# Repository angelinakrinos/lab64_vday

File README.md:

# **Lab64 Valentine's Day Music Box 🎵❤️**  
An Arduino-controlled music player for a Lab64 workshop, using an **ESP32C6**, **DFPlayer Mini**, and **RFID module** to create a customizable music box.

## **Workshop Instructions**  

### **Hardware Setup**  
#### 🔧 **Soldering Your Board**  
1. **Microcontroller (XIAO ESP32C6)**  
   - The **battery pads** on the back should be soldered first.  
   - Apply a small amount of solder to the pads before attaching the leads.  
   - Ensure the leads are inserted into the **thru holes** marked **BAT- and BAT+** (they are swapped—**double-check polarity!**).  
   - Solder header pins onto the microcontroller.  

2. **RFID Module**  
   - Solder **longer header pins** into your RFID module for better connection.  

3. **Soldering Components Onto the Board**  
   - **Terminal blocks** should face **outward** so wires can be easily inserted.  
   - The **battery holder** has clearly marked **positive and negative terminals**—pay attention to **snap-in orientation**.  
   - **RFID module** should be soldered as high as possible for better range.  

4. **Connecting Wires**  
   - Terminal blocks will connect to wires, which will connect to your peripherals (speaker, potentiometer, buttons, etc.).  

---

### **Software Setup**  
#### 💻 **Preparing Your Development Environment**  
1. Install **Arduino IDE** (if you haven’t already).  
2. Install the **XIAO ESP32C6 board configuration** in the Arduino IDE.  

#### 🚀 **Uploading the Code**  
- You need to **push the `vday_lab64_workshop_main.ino` code** to your **ESP32C6** for the music box to function.  
- Open `lab64_vday.ino` in Arduino IDE, select the correct **board (ESP32C6)** and **port**, then upload the code.  

#### 📀 **Writing RFID Tags & Playing Music**  
1. **RFID Writing**  
   - Use the provided `rfid_writer.ino` code to write RFID tags.  
   - The writer will **batch-write** tags **sequentially from 1 → ∞** (keep swiping cards to keep writing).  

2. **Music File Setup**  
   - Format your **microSD card to FAT32**.  
   - Inside the SD card, create a folder named **`mp3`**.  
   - Add your MP3 files inside the folder, naming them sequentially:  
     ```
     0001.mp3  
     0002.mp3  
     0003.mp3  
     ...
     ```
   - Insert the **SD card into the DFPlayer Mini** and **swipe an RFID tag** to play its corresponding track.  

---

### **Building the Music Box**  
#### 📦 **Assembling the Enclosure**  
1. Gather all the **box panels**.  
2. **Glue** the sides together using **wood glue**.  
3. **Before attaching the front panel**, install the **back panel** with fasteners—this is where peripherals like:  
   - 🎵 **Speaker**  
   - 🎛️ **Potentiometer**  
   - 🔘 **Buttons**  
   will be mounted.  
4. Customize the **lid** and print it to complete the box!  

🚀 **Enjoy your Valentine's Day Music Box!** 🎶❤️

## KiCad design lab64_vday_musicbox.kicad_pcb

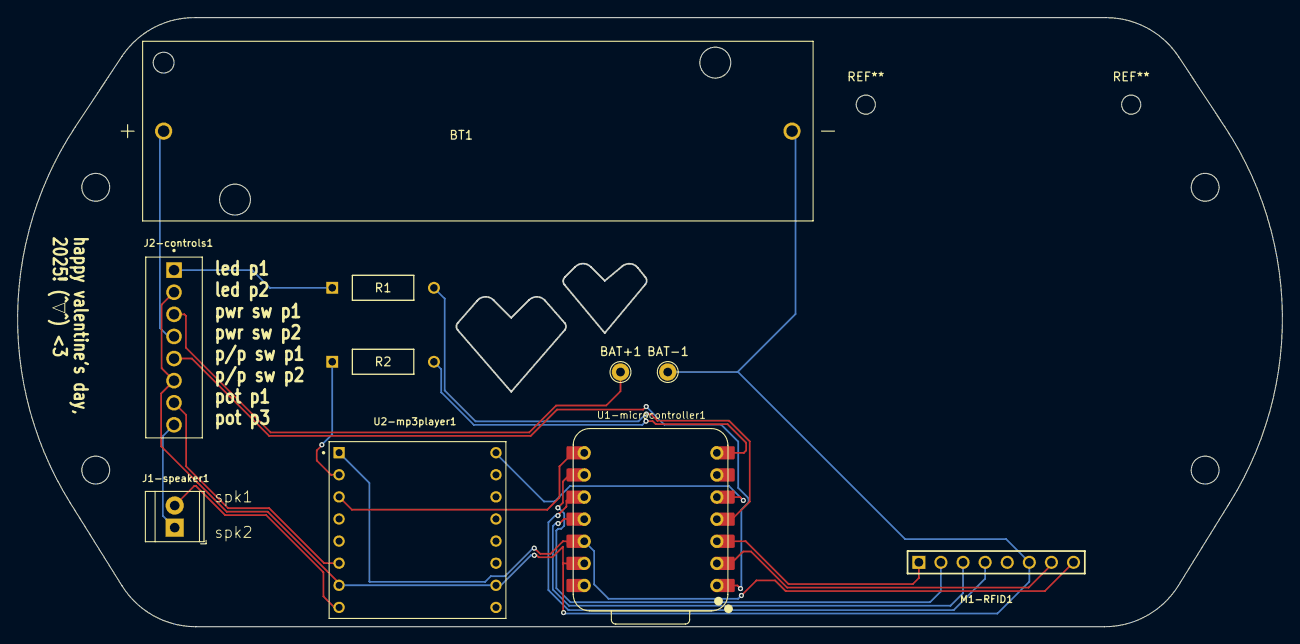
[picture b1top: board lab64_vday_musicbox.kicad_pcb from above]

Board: 2 copper layers, 145.4 x 70.0 mm, 10 parts (0 on the bottom side), 19 nets.

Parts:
BAT+1: TestPoint; TestPoint_THTPad_D2.0mm_Drill1.0mm
BAT-1: TestPoint; TestPoint_THTPad_D2.0mm_Drill1.0mm
BT1: 1043; BAT_1043
J1-speaker1: Screw_Terminal_01x02; TerminalBlock_TE_282834-2_1x02_P2.54mm_Horizontal
J2-controls1: Screw_Terminal_01x08; TE_282834-8
M1-RFID1: RFID-RC522
R1: 470; YAG_MF25_YAG
R2: 1K; YAG_MF25_YAG
U1-microcontroller1: XIAO-ESP32-S6-SMD; XIAO-ESP32C6-DIP
U2-mp3player1: DFR0299; MODULE_DFR0299

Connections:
+3.3V: M1-RFID1.8 (3V3), U1-microcontroller1.12 (3V3), U2-mp3player1.1 (VCC)
/GPIO: U1-microcontroller1.5 (GPIO22_D4_SDA), U2-mp3player1.16 (BUSY)
/LED1: J2-controls1.1, R1.1
/MISO: M1-RFID1.4 (MISO), U1-microcontroller1.10 (GPIO20_D9_MISO)
/MOSI: M1-RFID1.3 (MOSI), U1-microcontroller1.11 (GPIO18_D10_MOSI)
/POTP1: J1-speaker1.1, J2-controls1.8
/POTP2: J2-controls1.7, U2-mp3player1.6 (SPK1)
/RST: M1-RFID1.7 (RST), U1-microcontroller1.2 (GPIO1_A1_D1)
/RX_to_TX: U1-microcontroller1.8 (GPIO17_D7_RX), U2-mp3player1.3 (TX)
/SCK: M1-RFID1.2 (SCK), U1-microcontroller1.9 (GPIO19_D8_SCK)
/SS: M1-RFID1.1 (SDA), U1-microcontroller1.3 (GPIO2_A2_D2)
/SW1P1: BAT+1.1, J2-controls1.3
/SW1P2: BT1.P, J2-controls1.4
/SW2P1: J2-controls1.5, U1-microcontroller1.1 (GPIO0_A0_D0)
/TX_to_RX: R2.2, U1-microcontroller1.7 (GPIO16_D6_TX)
GND: BAT-1.1, BT1.N, J2-controls1.2, J2-controls1.6, M1-RFID1.6 (GND), U1-microcontroller1.13 (GND), U2-mp3player1.7 (GND), U2-mp3player1.10 (GND)
unnamed: J1-speaker1.2, U2-mp3player1.8 (SPK2)
unnamed: R1.2, U1-microcontroller1.4 (GPIO21_D3)
unnamed: R2.1, U2-mp3player1.2 (RX)

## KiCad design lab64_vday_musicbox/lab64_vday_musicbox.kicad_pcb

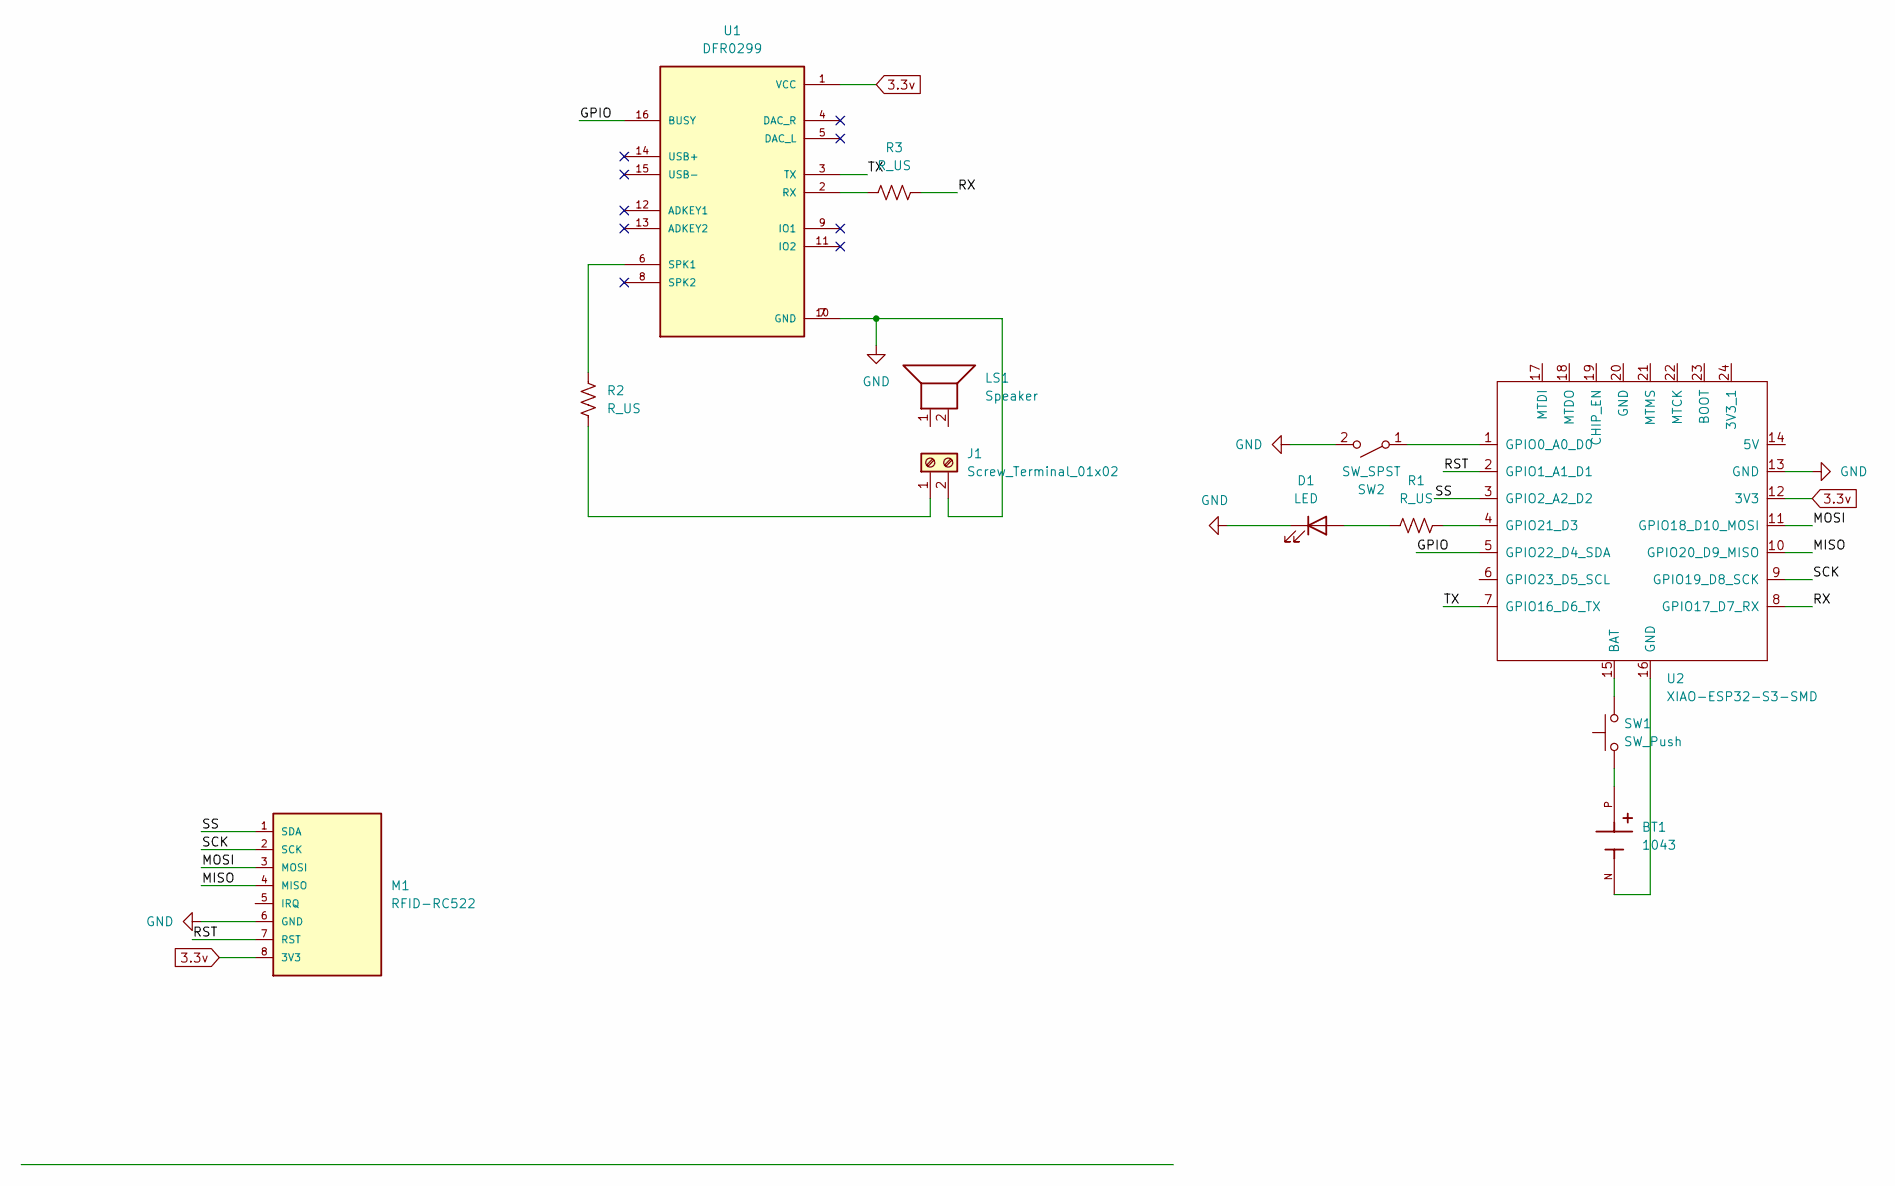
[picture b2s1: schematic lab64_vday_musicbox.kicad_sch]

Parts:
BT1: 1043; BAT_1043; PARTREV J
D1: LED; LED-APA102-2020
J1: Screw_Terminal_01x02; TerminalBlock_WAGO_236-102_1x02_P5.00mm_45Degree
LS1: Speaker
M1: RFID-RC522; MPN RFID-RC522
R1, R2, R3: R_US; R_0201_0603Metric
SW1: SW_Push; SW_Push_1P1T-SH_NO_CK_KMR2xxG
SW2: SW_SPST; SW_DIP_SPSTx01_Slide_6.7x4.1mm_W6.73mm_P2.54mm_LowProfile_J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
U1: DFR0299; MODULE_DFR0299
U2: XIAO-ESP32-S3-SMD; XIAO-ESP32C6-SMD

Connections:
3.3v: M1.8 (3V3), U1.1 (VCC), U2.12 (3V3)
/GPIO: U1.16 (BUSY), U2.5 (GPIO22_D4_SDA)
/MISO: M1.4 (MISO), U2.10 (GPIO20_D9_MISO)
/MOSI: M1.3 (MOSI), U2.11 (GPIO18_D10_MOSI)
/RST: M1.7 (RST), U2.2 (GPIO1_A1_D1)
/RX: R3.2, U2.8 (GPIO17_D7_RX)
/SCK: M1.2 (SCK), U2.9 (GPIO19_D8_SCK)
/SS: M1.1 (SDA), U2.3 (GPIO2_A2_D2)
/TX: U1.3 (TX), U2.7 (GPIO16_D6_TX)
GND: D1.1 (K), J1.2, M1.6 (GND), SW2.2 (B), U1.7 (GND), U1.10 (GND), U2.13 (GND)
unnamed: BT1.N, U2.16 (GND)
unnamed: BT1.P, SW1.1
unnamed: D1.2 (A), R1.1
unnamed: J1.1, R2.1
unnamed: SW2.1 (A), U2.1 (GPIO0_A0_D0)
unnamed: R3.1, U1.2 (RX)
unnamed: R2.2, U1.6 (SPK1)
unnamed: SW1.2, U2.15 (BAT)
unnamed: R1.2, U2.4 (GPIO21_D3)

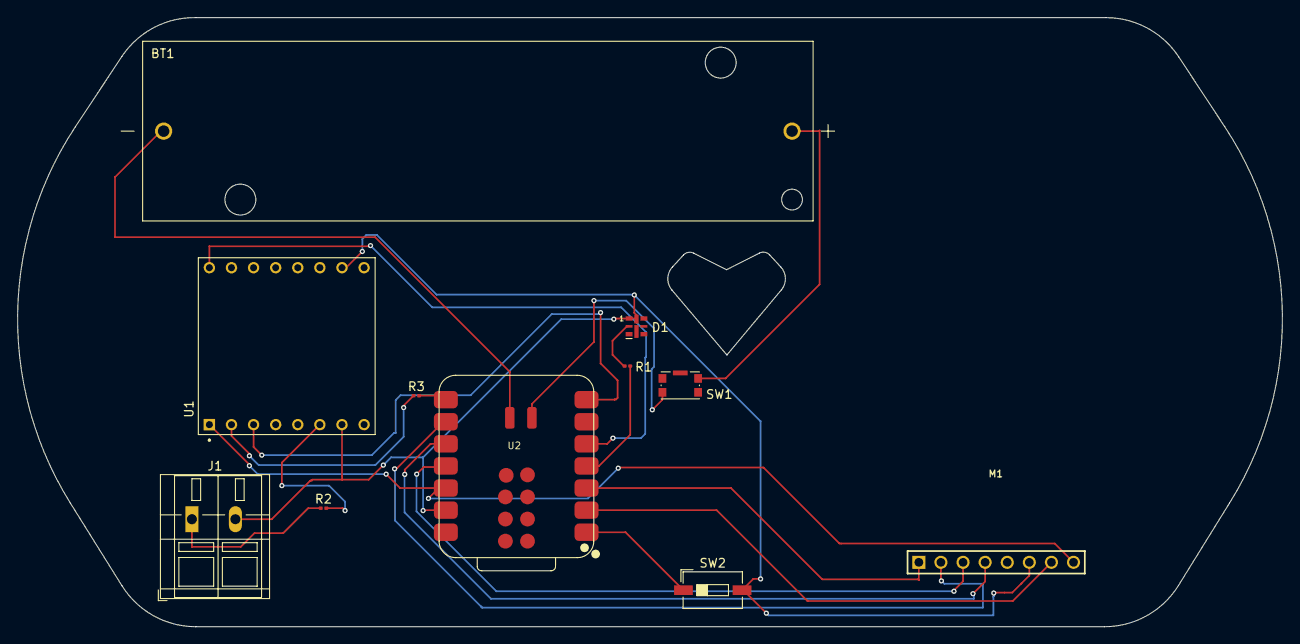
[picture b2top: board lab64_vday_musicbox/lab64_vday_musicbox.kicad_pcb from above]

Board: 2 copper layers, 145.4 x 70.0 mm, 11 parts (0 on the bottom side), 19 nets.

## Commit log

2025-02-08 adding final pcb files
2025-02-14 Create code
2025-02-14 Create X
2025-02-14 Create module_testers
2025-02-17 Bugfixes for code; more detail in README
2025-02-17 Trailing newline for .gitignore
2025-02-18 fixed incorrect BUSY_PIN
2025-04-26 Rename 2EBABA8D-8C7A-4B70-9168-52EE7FFD091B.jpeg to red_board_layout
2025-04-26 Rename 82991383-BDF9-41F9-A83C-D66BC992F94A.jpeg to red_board_schematic
2025-04-26 Rename ref_photos/lab64_vday_pcb.jpg to ref_photos/green_board_pics/green_board_layout.jpg
2025-04-26 Rename ref_photos/lab64_vday_schematic.pdf to ref_photos/green_board_pics/green_board_schematic
2025-04-26 Rename ref_photos/soldered_board.JPG to ref_photos/green_board_pics/green_soldered_board.JPG
2025-06-06 Rename Valentines Box v4 (1).zip to Valentines Box box NEWEST VERSION.zip
